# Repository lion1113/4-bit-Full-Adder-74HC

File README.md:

# 4 bit 74HC Full Adder

This is a 4 bit Adder, made to work with 74HC ICs. I made this as a school project. The project was made with KiCAD 9.0.
Thanks to @nbellotto who helped me along the way. 
I do not intend to update this, but feel free to fork the repository and modify it to your liking, as long as you comply with the [license](./License)

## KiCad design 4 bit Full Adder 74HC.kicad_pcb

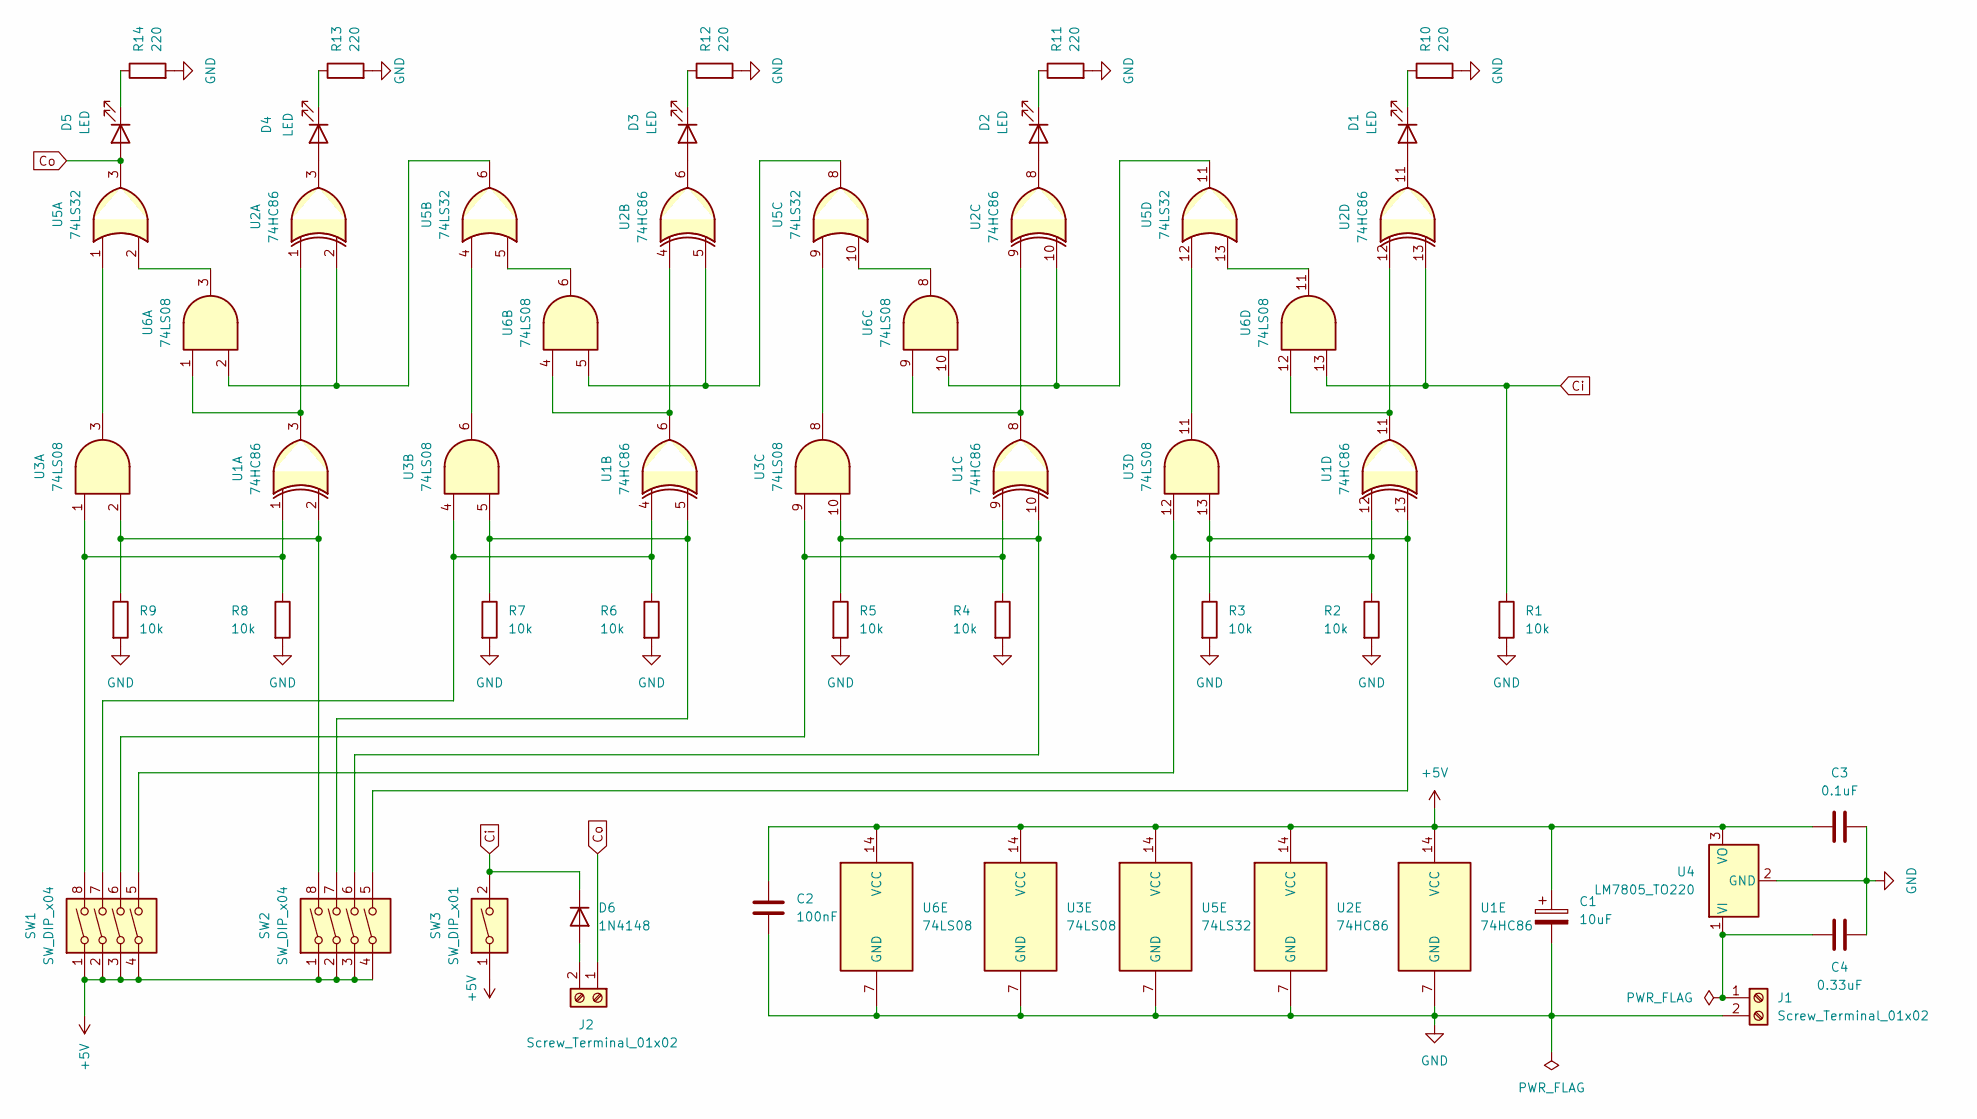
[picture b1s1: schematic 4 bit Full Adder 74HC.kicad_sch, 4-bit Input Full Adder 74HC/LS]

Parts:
C1: 10uF; CP_Radial_D5.0mm_P2.50mm
C2: 100nF; C_Rect_L7.0mm_W2.0mm_P5.00mm
C3: 0.1uF; C_Rect_L7.0mm_W2.0mm_P5.00mm
C4: 0.33uF; C_Rect_L7.0mm_W2.0mm_P5.00mm
D1, D2, D3, D4, D5: LED; LED_D3.0mm
D6: 1N4148; D_DO-35_SOD27_P7.62mm_Horizontal
J1, J2: Screw_Terminal_01x02; TerminalBlock_Phoenix_MKDS-1,5-2-5.08_1x02_P5.08mm_Horizont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
R1, R2, R3, R4, R5, R6, R7, R8, R9: 10k; R_Axial_DIN0207_L6.3mm_D2.5mm_P10.16mm_Horizontal
R10, R11, R12, R13, R14: 220; R_Axial_DIN0207_L6.3mm_D2.5mm_P10.16mm_Horizontal
SW1, SW2: SW_DIP_x04; SW_DIP_SPSTx04_Slide_9.78x12.34mm_W7.62mm_P2.54mm
SW3: SW_DIP_x01; SW_DIP_SPSTx01_Slide_9.78x4.72mm_W7.62mm_P2.54mm
U1, U2: 74HC86; DIP-14_W7.62mm_LongPads
U3, U6: 74LS08; DIP-14_W7.62mm_LongPads
U4: LM7805_TO220; TO-220-3_Vertical
U5: 74LS32; DIP-14_W7.62mm_LongPads

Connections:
+5V: C1.1, C2.1, C3.1, SW1.1, SW1.2, SW1.3, SW1.4, SW2.1, SW2.2, SW2.3, SW2.4, SW3.1, U1.14 (VCC), U2.14 (VCC), U3.14 (VCC), U4.3 (VO), U5.14 (VCC), U6.14 (VCC)
Ci: D6.1 (K), R1.1, SW3.2, U2.13, U6.13
Co: D5.2 (A), J2.1, U5.3
GND: C1.2, C2.2, C3.2, C4.2, J1.2, R1.2, R2.2, R3.2, R4.2, R5.2, R6.2, R7.2, R8.2, R9.2, R10.2, R11.2, R12.2, R13.2, R14.2, U1.7 (GND), U2.7 (GND), U3.7 (GND), U4.2 (GND), U5.7 (GND), U6.7 (GND)
unnamed: D1.2 (A), U2.11
unnamed: D1.1 (K), R10.1
unnamed: D2.2 (A), U2.8
unnamed: D2.1 (K), R11.1
unnamed: D3.2 (A), U2.6
unnamed: D3.1 (K), R12.1
unnamed: D4.2 (A), U2.3
unnamed: D4.1 (K), R13.1
unnamed: D5.1 (K), R14.1
unnamed: D6.2 (A), J2.2
unnamed: C4.1, J1.1, U4.1 (VI)
unnamed: R2.1, SW1.5, U1.12, U3.12
unnamed: R3.1, SW2.5, U1.13, U3.13
unnamed: R4.1, SW1.6, U1.9, U3.9
unnamed: R5.1, SW2.6, U1.10, U3.10
unnamed: R6.1, SW1.7, U1.4, U3.4
unnamed: R7.1, SW2.7, U1.5, U3.5
unnamed: R8.1, SW1.8, U1.1, U3.1
unnamed: R9.1, SW2.8, U1.2, U3.2
unnamed: U1.3, U2.1, U6.1
unnamed: U1.6, U2.4, U6.4
unnamed: U1.8, U2.9, U6.9
unnamed: U1.11, U2.12, U6.12
unnamed: U2.2, U5.6, U6.2
unnamed: U2.5, U5.8, U6.5
unnamed: U2.10, U5.11, U6.10
unnamed: U3.3, U5.1
unnamed: U3.6, U5.4
unnamed: U3.8, U5.9
unnamed: U3.11, U5.12
unnamed: U5.2, U6.3
unnamed: U5.5, U6.6
unnamed: U5.10, U6.8
unnamed: U5.13, U6.11

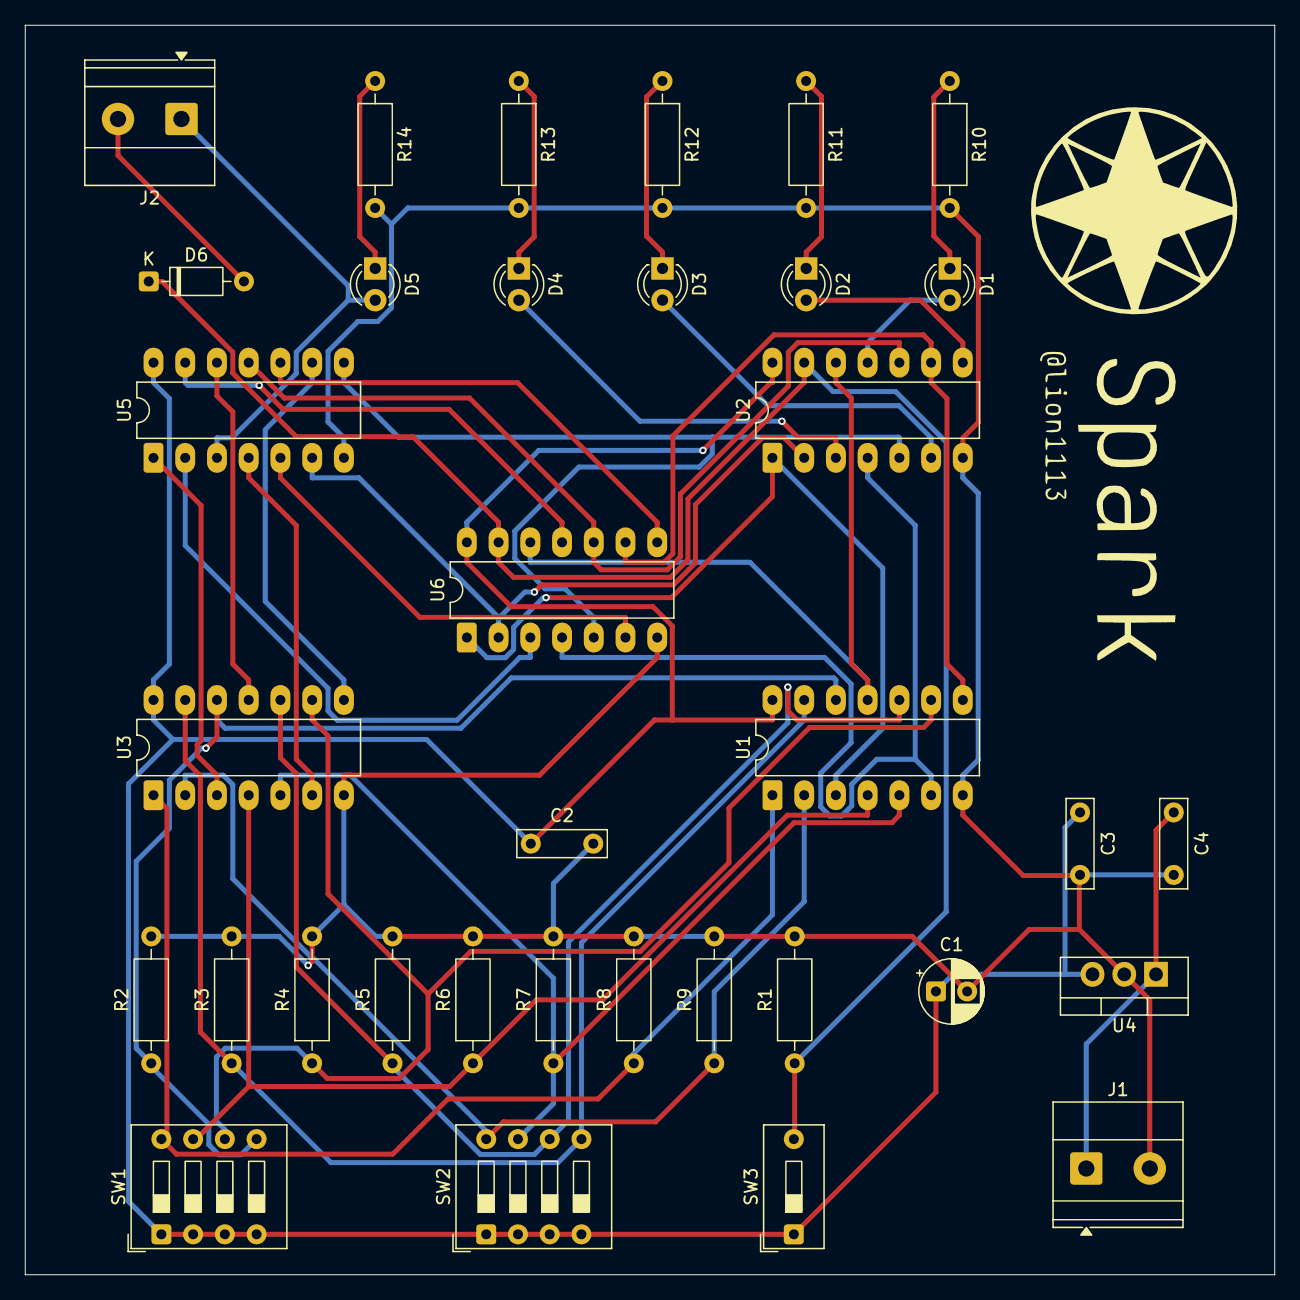
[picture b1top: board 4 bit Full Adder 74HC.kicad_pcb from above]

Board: 2 copper layers, 100.0 x 100.0 mm, 35 parts (0 on the bottom side), 38 nets.

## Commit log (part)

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2025-12-24 Added Schematic PDF
2025-12-28 Update PCB
2026-05-16 Update name and fabrication files
2026-05-16 Github
